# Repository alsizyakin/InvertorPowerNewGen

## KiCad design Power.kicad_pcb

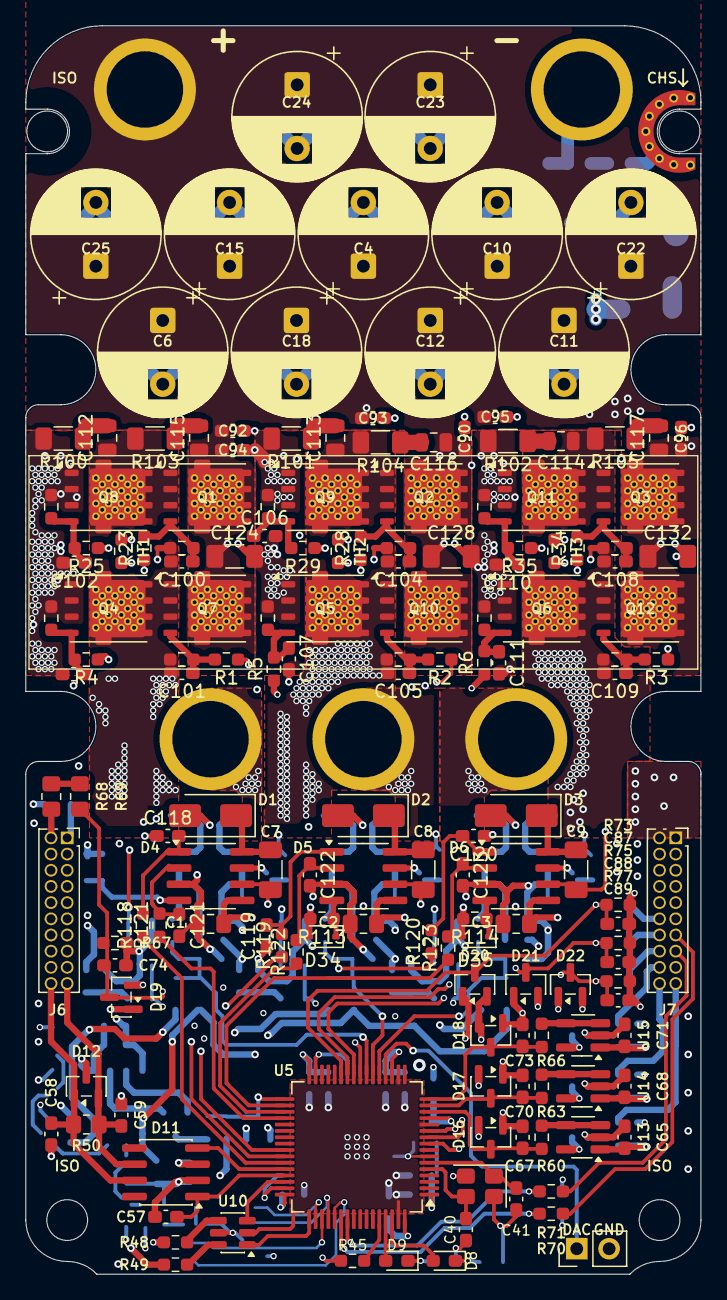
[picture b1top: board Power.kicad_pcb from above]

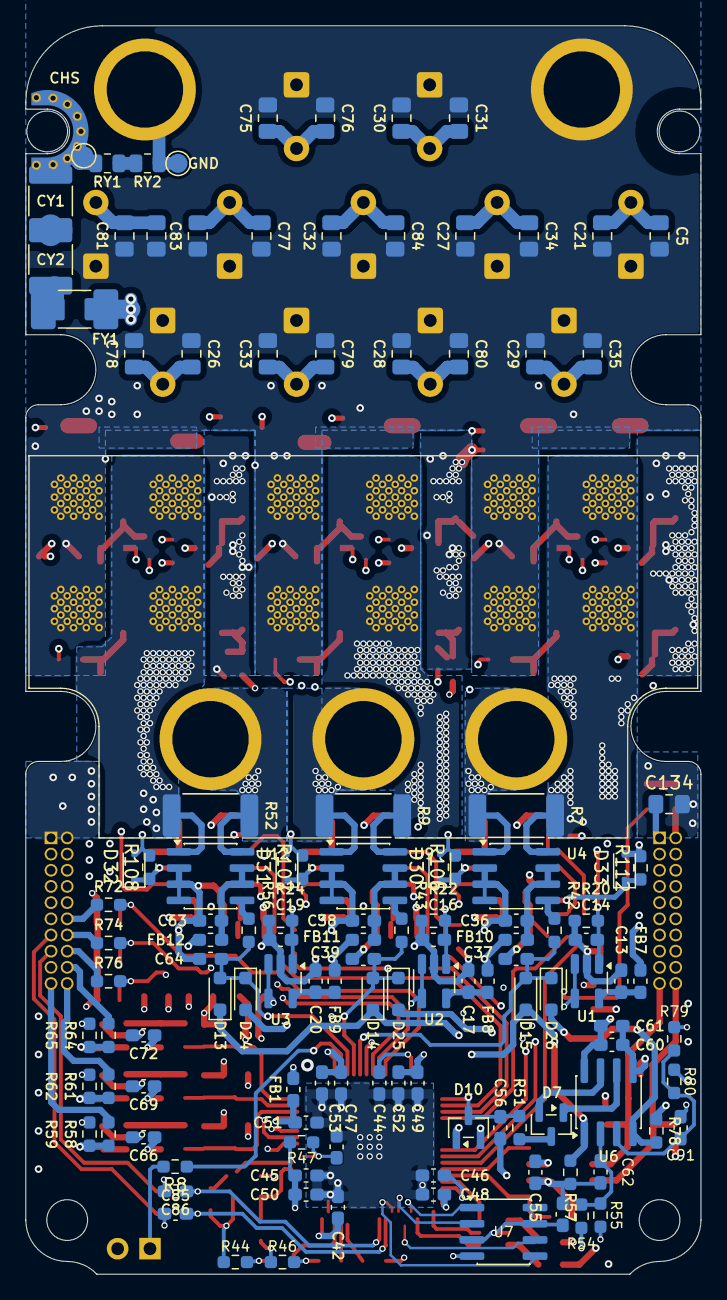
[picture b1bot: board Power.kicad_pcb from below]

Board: 6 copper layers, 53.0 x 98.0 mm, 299 parts (126 on the bottom side), 139 nets.

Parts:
C1, C2, C3: 10u; C_0805_2012Metric_Pad1.18x1.45mm_HandSolder
C4, C6, C10, C11, C12, C15, C18, C22, C23, C24, C25: 180u; CP_Radial_D10.0mm_P5.00mm
C5, C21, C26, C27, C28, C29, C30, C31, C32, C33, C34, C35, C75, C76, C77, C78, C79, C80, C81, C82, C83, C84: 2.2u; C_0805_2012Metric_Pad1.18x1.45mm_HandSolder
C7, C8, C9: 1u; C_1206_3216Metric_Pad1.33x1.80mm_HandSolder
C13, C14, C16, C17, C19, C20, C36, C38, C42, C43, C45, C47, C48, C49, C50, C61, C62, C63, C66, C69, C72, C74, C91: 100n; C_0603_1608Metric_Pad1.08x0.95mm_HandSolder
C37, C39, C64: 15n; C_0603_1608Metric_Pad1.08x0.95mm_HandSolder
C40, C41: 12p; C_0603_1608Metric_Pad1.08x0.95mm_HandSolder
C44, C46, C60, C90, C92, C93, C94, C95, C96: 2.2u; C_0603_1608Metric_Pad1.08x0.95mm_HandSolder
C51: 10u; C_0603_1608Metric_Pad1.08x0.95mm_HandSolder
C52: 4.7u; C_0603_1608Metric_Pad1.08x0.95mm_HandSolder
C53, C54, C55: 1u; C_0603_1608Metric_Pad1.08x0.95mm_HandSolder
C56: 10p; C_0603_1608Metric_Pad1.08x0.95mm_HandSolder
C57, C58, C59, C67, C70, C73: 56p; C_0603_1608Metric_Pad1.08x0.95mm_HandSolder
C65, C68, C71, C87, C88, C89: 1n; C_0603_1608Metric_Pad1.08x0.95mm_HandSolder
C85, C86: 10n; C_0603_1608Metric_Pad1.08x0.95mm_HandSolder
C100, C101, C102, C103, C104, C105, C106, C107, C108, C109, C110, C111: 10n 50V C0G; C_0603_1608Metric_Pad1.08x0.95mm_HandSolder
C112, C113, C114, C115, C116, C117: 4.7n 100V C0G; C_0805_2012Metric
C118, C119, C120, C121, C122, C123: 100p; C_0603_1608Metric_Pad1.08x0.95mm_HandSolder
C124, C128, C132: 1u 100V X7R; C_1206_3216Metric_Pad1.33x1.80mm_HandSolder
C134: 100n 100V X7R; C_0805_2012Metric_Pad1.18x1.45mm_HandSolder
CY1, CY2: 470n 250V X7R; C_1812_4532Metric
D1, D2, D3: D_SMA
D4, D5, D6, D11: SOIC-8_3.9x4.9mm_P1.27mm
D7, D10, D12, D16, D17, D18, D19, D20, D21, D22: SOT-23
D8, D9: LED_0603_1608Metric_Pad1.05x0.95mm_HandSolder
D13, D14, D15, D24, D25, D26: D_SOD-323_HandSoldering
D30, D31, D32, D33, D34, D35: PMEG4010BEA; D_SOD-323
FB1, FB7, FB8, FB9, FB10, FB11, FB12: L_0603_1608Metric_Pad1.05x0.95mm_HandSolder
FY1: 2A 125VDC; Fuse_2410_1206
H1, H3, H4: MountingHole; MountingHole_3.2mm_M3
H2: H_CHS; MountingHole_3.2mm_M3_Slot_CHS
J1, J2, J3, J4, J5: Bush_M4
J6, J7: PinSocket_2x10_P1.27mm_Vertical
NT1, NT2, NT3: NetTie_2; NetTie-2_SMD_Pad0.5mm
Q1, Q2, Q3, Q4, Q5, Q6, Q7, Q8, Q9, Q10, Q11, Q12: PDFN-8L
R1, R2, R3, R4, R5, R6, R23, R25, R28, R29, R34, R35: 1; R_0603_1608Metric_Pad0.98x0.95mm_HandSolder
R7, R9, R52: 300u; R_2512_6332Metric_Pad1.40x3.35mm_HandSolder
R8: R; R_0603_1608Metric_Pad0.98x0.95mm_HandSolder
R19, R20, R21, R22, R24, R26, R27, R30, R31, R32, R33, R36, R37, R38, R39, R45, R47, R57, R78: 10k; R_0603_1608Metric_Pad0.98x0.95mm_HandSolder
R42, R43, R56, R60, R63, R66, R70, R71: 120; R_0603_1608Metric_Pad0.98x0.95mm_HandSolder
R44, R46, R67: 1k; R_0603_1608Metric_Pad0.98x0.95mm_HandSolder
R48, R49: 20; R_0603_1608Metric_Pad0.98x0.95mm_HandSolder
R50: 120; R_0805_2012Metric_Pad1.20x1.40mm_HandSolder
R51: 100; R_0603_1608Metric_Pad0.98x0.95mm_HandSolder
R54: 5.6k; R_0603_1608Metric_Pad0.98x0.95mm_HandSolder
R55, R58, R61, R64, R72, R74, R76: 18k; R_0603_1608Metric_Pad0.98x0.95mm_HandSolder
R59, R62, R65, R73, R75, R77: 36k; R_0603_1608Metric_Pad0.98x0.95mm_HandSolder
R68, R69: 16.2k; R_0805_2012Metric_Pad1.20x1.40mm_HandSolder
R79: 2.4k; R_0603_1608Metric_Pad0.98x0.95mm_HandSolder
R80: 750; R_0603_1608Metric_Pad0.98x0.95mm_HandSolder
R100, R101, R102, R103, R104, R105: 0.47; R_1206_3216Metric_Pad1.30x1.75mm_HandSolder
R106, R107, R108, R112, R113, R114: 0.82; R_0603_1608Metric_Pad0.98x0.95mm_HandSolder
R118, R119, R120, R121, R122, R123: 0; R_0603_1608Metric_Pad0.98x0.95mm_HandSolder
RY1, RY2: 100k; R_0805_2012Metric
TH1, TH2, TH3: R_0603_1608Metric_Pad0.98x0.95mm_HandSolder
TP1: DAC1; PinHeader_1x02_P2.54mm_Vertical
TP2: TP_CHS; TestPoint_Pad_D1.5mm
TP3: TP_GND; TestPoint_Pad_D1.5mm
U1, U2, U3, U13, U14, U15: SOT-23-5_HandSoldering
U4, U6, U7, U9, U12: SOIC-8_3.9x4.9mm_P1.27mm
U5: LQFP-64_10x10mm_P0.5mm
U10: SOT-23-6
Y1: 16M; Crystal_SMD_SeikoEpson_FA238-4Pin_3.2x2.5mm

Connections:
+3.3V: C42.1, C45.1, C47.1, C48.1, C49.1, C50.1, C52.1, C53.1, C54.1, C55.2, C60.1, C61.1, C66.1, C69.1, C72.1, D10.2 (K), D11.3 (Vcc), D16.2 (K), D17.2 (K), D18.2 (K), D19.2 (K), D20.2 (K), D21.2 (K), D22.2 (K), FB1.2, FB7.1, FB8.1, FB9.1, FB10.1, FB11.1, FB12.1, J7.7, J7.8, J7.9, J7.10, R47.1, R54.1, R78.1, R79.1, TH1.1, TH2.1, TH3.1, U5.1 (VBAT), U5.19 (VDD), U5.32 (VDD), U5.48 (VDD), U5.64 (VDD), U6.8 (V+), U7.3 (~WP), U7.7 (~HOLD), U7.8 (VCC), U10.5 (VBUS), U13.5 (V+), U14.5 (V+), U15.5 (V+)
+3.3VA: C51.1, FB1.1, U5.13 (VDDA)
+12V: C1.2, C2.2, C3.2, D1.2 (A), D2.2 (A), D3.2 (A), D4.5 (VDD), D5.5 (VDD), D6.5 (VDD), J6.7, J6.8, J6.9, J6.10
/ADC_IN_1: C89.1, D22.3 (A), R76.2, R77.1, U5.25 (PC5)
/ADC_IN_2: C88.1, D21.3 (A), R74.2, R75.1, U5.26 (PB0)
/ADC_IN_3: C87.1, D20.3 (A), R72.2, R73.1, U5.27 (PB1)
/BkIN_1: C56.1, D10.3 (common), R51.1, U5.33 (PB12)
/CAN1_RXD_MCU: D11.4 (R), U5.44 (PA11)
/CAN1_TXD_MCU: C57.2, D11.1 (D), U5.45 (PA12)
/CANH: C58.2, D11.7 (CANH), D12.1 (K), J6.20, R50.2
/CANL: C59.1, D11.6 (CANL), D12.2 (K), J6.19, R50.1
/CHASSIS: CY1.1, H2.1, RY1.1, TP2.1
/CY_MID: CY1.2, CY2.1
/Current_Sensor_1/Phase_IN: C108.2, C109.2, C114.1, NT3.2, Q3.S, Q6.D, Q11.D, Q12.S, R36.1, R38.1, R52.2, R105.2, U12.1 (IN-)
/Current_Sensor_1/Phase_OUT: J3.1 (Pin_1_1), R52.1, U12.8 (IN+)
/Current_Sensor_2/Phase_IN: C104.2, C105.2, C113.1, NT2.2, Q2.S, Q5.D, Q9.D, Q10.S, R9.2, R30.1, R32.1, R104.2, U9.8 (IN+)
/Current_Sensor_2/Phase_OUT: J2.1 (Pin_1_1), R9.1, U9.1 (IN-)
/Current_Sensor_3/Phase_IN: C100.2, C101.2, C112.1, NT1.2, Q1.S, Q4.D, Q7.S, Q8.D, R7.1, R19.1, R26.1, R103.2, U4.8 (IN+)
/Current_Sensor_3/Phase_OUT: J1.1 (Pin_1_1), R7.2, U4.1 (IN-)
/Current_measure_1: C64.2, D13.2 (A), D24.1 (K), R56.1, U5.21 (PA5)
/Current_measure_2: C39.2, D14.2 (A), D25.1 (K), R43.1, U5.22 (PA6)
/Current_measure_3: C37.2, D15.2 (A), D26.1 (K), R42.1, U5.23 (PA7)
/DAC_1_MCU: R8.1, U5.20 (PA4)
/Digital_IN/OUT_1: C85.2, R70.1, U5.54 (PD2)
/Digital_IN/OUT_2: C86.1, R71.2, U5.55 (PB3)
/Driver_1/HO: D32.2 (A), R3.1, R34.1, R108.2
/Driver_1/HO_DRV: D6.7 (HO), D32.1 (K), R108.1
/Driver_1/LO: D35.2 (A), R6.1, R35.1, R114.2
/Driver_1/LO_DRV: D6.4 (LO), D35.1 (K), R114.1
/Driver_1/SW: C9.2, D6.6 (SW), NT3.1
/Driver_2/HO: D31.2 (A), R2.1, R28.1, R107.2
/Driver_2/HO_DRV: D5.7 (HO), D31.1 (K), R107.1
/Driver_2/LO: D34.2 (A), R5.1, R29.1, R113.2
/Driver_2/LO_DRV: D5.4 (LO), D34.1 (K), R113.1
/Driver_2/SW: C8.2, D5.6 (SW), NT2.1
/Driver_3/HO: D30.2 (A), R1.1, R23.1, R106.2
/Driver_3/HO_DRV: D4.7 (HO), D30.1 (K), R106.1
/Driver_3/LO: D33.2 (A), R4.1, R25.1, R112.2
/Driver_3/LO_DRV: D4.4 (LO), D33.1 (K), R112.1
/Driver_3/SW: C7.2, D4.6 (SW), NT1.1
/EEPROM_MISO_MCU: U5.52 (PC11), U7.2 (MISO)
/EEPROM_MOSI_MCU: U5.53 (PC12), U7.5 (MOSI)
/EEPROM_SCK_MCU: U5.51 (PC10), U7.6 (SCK)
/EEPROM_~CS_MCU: U5.50 (PA15), U7.1 (~CS)
/HALL_1: J7.19, R58.1
/HALL_2: J7.20, R61.1
/HALL_3: J7.18, R64.1
/Hall_1_MCU: C67.1, D16.3 (A), R60.2, U5.14 (PA0)
/Hall_2_MCU: C70.1, D17.3 (A), R63.2, U5.15 (PA1)
/Hall_3_MCU: C73.1, D18.3 (A), R66.2, U5.16 (PA2)
/RY_MID: RY1.2, RY2.1
/SWCLK: U5.49 (PA14), U10.1 (I/O1)
/SWCLK_IN: J6.15, R49.2
/SWDIO: U5.46 (PA13), U10.3 (I/O2)
/SWDIO_IN: J6.13, R48.2
/TMR1_CH1: R120.1, U5.41 (PA8)
/TMR1_CH1N: R123.1, U5.34 (PB13)
/TMR1_CH2: R119.1, U5.42 (PA9)
/TMR1_CH2N: R122.1, U5.35 (PB14)
/TMR1_CH3: R118.1, U5.43 (PA10)
/TMR1_CH3N: R121.1, U5.36 (PB15)
/Temp_PCB_1_MCU: U3.3 (-), U3.4, U5.9 (PC1)
/Temp_PCB_2_MCU: U2.3 (-), U2.4, U5.10 (PC2)
/Temp_PCB_3_MCU: U1.3 (-), U1.4, U5.11 (PC3)
/VDC_MCU: C74.1, D19.3 (A), R67.1, R69.2, U5.24 (PC4)
/Y_F: CY2.2, FY1.2
BOOT0: R45.2, U5.60 (BOOT0)
GND: C1.1, C2.1, C3.1, C4.2, C5.2, C6.2, C10.2, C11.2, C12.2, C13.2, C14.1, C15.2, C16.1, C17.2, C18.2, C19.1, C20.2, C21.2, C22.2, C23.2, C24.2, C25.2, C26.2, C27.2, C28.2, C29.2, C30.2, C31.2, C32.2, C33.2, C34.2, C35.2, C36.1, C37.1, C38.1, C39.1, C40.1, C41.2, C42.2, C43.1, C44.2, C45.2, C46.2, C47.2, C48.2, C49.2, C50.2, C51.2, C52.2, C53.2, C54.2, C55.1, C56.2, C57.1, C58.1, C59.2, C60.2, C61.2, C62.2, C63.1, C64.1, C65.2, C66.2, C67.2, C68.2, C69.2, C70.2, C71.2, C72.2, C73.2, C74.2, C75.2, C76.2, C77.2, C78.2, C79.2, C80.2, C81.2, C82.2, C83.2, C84.2, C85.1, C86.2, C87.2, C88.2, C89.2, C90.2, C91.2, C92.2, C93.2, C94.2, C95.2, C96.2, C102.2, C103.2, C106.2, C107.2, C110.2, C111.2, C118.1, C119.1, C120.1, C121.2, C122.2, C123.2, C124.2, C128.2, C132.2, C134.2, D4.3 (GND), D5.3 (GND), D6.3 (GND), D10.1 (A), D11.2 (GND), D12.3 (A), D16.1 (K), D17.1 (K), D18.1 (K), D19.1 (K), D20.1 (K), D21.1 (K), D22.1 (K), FY1.1, J5.1 (Pin_1_1), J6.11, J6.12, J6.17, J6.18, J7.1, J7.2, J7.3, J7.4, J7.5, J7.6, J7.11, J7.17, Q4.S, Q5.S, Q6.S, Q8.S, Q9.S, Q11.S, R20.1, R21.1, R22.1, R24.1, R27.1, R31.1, R33.1, R37.1, R39.1, R44.2, R45.1, R46.2, R55.2, R57.1, R59.2, R62.2, R65.2, R67.2, R73.2, R75.2, R77.2, R80.2, R100.2, R101.2, R102.2, RY2.2, TP1.2, TP3.1, U1.2 (V-), U2.2 (V-), U3.2 (V-), U4.2 (GND), U4.3 (REF2), U4.4 (NC), U5.12 (VSSA), U5.18 (VSS), U5.63 (VSS), U6.5 (V-), U7.4 (GND), U9.2 (GND), U9.3 (REF2), U9.4 (NC), U10.2 (GND), U12.2 (GND), U12.3 (REF2), U12.4 (NC), U13.2 (V-), U14.2 (V-), U15.2 (V-), Y1.2, Y1.4
NRST: C43.2, R47.2, U5.7 (NRST)
unnamed: C100.1, Q1.G, R19.2, R23.2
unnamed: C101.1, Q7.G, R1.2, R26.2
unnamed: C102.1, Q8.G, R21.2, R25.2
unnamed: C103.1, Q4.G, R4.2, R27.2
unnamed: C104.1, Q2.G, R28.2, R30.2
unnamed: C105.1, Q10.G, R2.2, R32.2
unnamed: C106.1, Q9.G, R29.2, R31.2
unnamed: C107.1, Q5.G, R5.2, R33.2
unnamed: C108.1, Q3.G, R34.2, R36.2
unnamed: C109.1, Q12.G, R3.2, R38.2
unnamed: C110.1, Q11.G, R35.2, R37.2
unnamed: C111.1, Q6.G, R6.2, R39.2
unnamed: C112.2, R100.1
unnamed: C113.2, R101.1
unnamed: C114.2, R102.1
unnamed: C115.2, R103.1
unnamed: C116.2, R104.1
unnamed: C117.2, R105.1
unnamed: C7.1, D1.1 (K), D4.8 (BST)
unnamed: C8.1, D2.1 (K), D5.8 (BST)
unnamed: C9.1, D3.1 (K), D6.8 (BST)
unnamed: C118.2, D4.1 (HI), R118.2
unnamed: C121.1, D4.2 (LI), R121.2
unnamed: C119.2, D5.1 (HI), R119.2
unnamed: C122.1, D5.2 (LI), R122.2
unnamed: C120.2, D6.1 (HI), R120.2
unnamed: C123.1, D6.2 (LI), R123.2
unnamed: D7.1, U6.6
unnamed: D7.2, U6.7
unnamed: D7.3, R51.2
unnamed: D8.2 (A), U5.62 (PB9)
unnamed: D8.1 (K), R44.1
unnamed: D9.2 (A), U5.61 (PB8)
unnamed: D9.1 (K), R46.1
unnamed: D13.1 (K), D14.1 (K), D15.1 (K), R57.2, U6.1 (+)
unnamed: D24.2 (A), D25.2 (A), D26.2 (A), R78.2, U6.4 (-)
unnamed: J7.12, R72.1
unnamed: J7.13, R70.2
unnamed: J7.14, R74.1
unnamed: J7.15, R71.1
unnamed: J7.16, R76.1
unnamed: R8.2, TP1.1
unnamed: R48.1, U10.4 (I/O2)
unnamed: R49.1, U10.6 (I/O1)
unnamed: R68.2, R69.1
unnamed: C14.2, R20.2, TH1.2, U1.1 (+)
unnamed: C13.1, FB7.2, U1.5 (V+)
unnamed: C16.2, R22.2, TH2.2, U2.1 (+)
unnamed: C17.1, FB8.2, U2.5 (V+)
unnamed: C19.2, R24.2, TH3.2, U3.1 (+)
unnamed: C20.1, FB9.2, U3.5 (V+)
unnamed: R42.2, U4.5 (OUT)
unnamed: C36.2, FB10.2, U4.6 (VS), U4.7 (REF1)
unnamed: C40.2, U5.5 (PH0), Y1.3
unnamed: C41.1, U5.6 (PH1), Y1.1
unnamed: C44.1, U5.31 (VCAP_1)
unnamed: C46.1, U5.47 (VCAP_2)
unnamed: C62.1, R54.2, R55.1, U6.2 (-)
unnamed: C91.1, R79.2, R80.1, U6.3 (+)
unnamed: R43.2, U9.5 (OUT)
unnamed: C38.2, FB11.2, U9.6 (VS), U9.7 (REF1)
unnamed: R56.2, U12.5 (OUT)
unnamed: C63.2, FB12.2, U12.6 (VS), U12.7 (REF1)
unnamed: C65.1, R58.2, R59.1, U13.1 (+)
unnamed: R60.1, U13.3 (-), U13.4
unnamed: C68.1, R61.2, R62.1, U14.1 (+)
unnamed: R63.1, U14.3 (-), U14.4
unnamed: C71.1, R64.2, R65.1, U15.1 (+)
unnamed: R66.1, U15.3 (-), U15.4
VDC: C4.1, C5.1, C6.1, C10.1, C11.1, C12.1, C15.1, C18.1, C21.1, C22.1, C23.1, C24.1, C25.1, C26.1, C27.1, C28.1, C29.1, C30.1, C31.1, C32.1, C33.1, C34.1, C35.1, C75.1, C76.1, C77.1, C78.1, C79.1, C80.1, C81.1, C82.1, C83.1, C84.1, C90.1, C92.1, C93.1, C94.1, C95.1, C96.1, C115.1, C116.1, C117.1, C124.1, C128.1, C132.1, C134.1, J4.1 (Pin_1_1), J6.1, J6.2, J6.3, J6.4, Q1.D, Q2.D, Q3.D, Q7.D, Q10.D, Q12.D, R68.1

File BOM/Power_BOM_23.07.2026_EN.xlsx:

Reference | Value | Product Name | Replacement | Package | Description | Quantity | DNP
C13, C14, C16, C17, C19, C20, C36, C37, C38, C39, C42, C43, C45, C47, C48, C49,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 | 100n |  |  | SMD 0603 | Capacitor SMD 50V | 26
C85, C86 | 10n |  |  | SMD 0603 | Capacitor SMD 50V | 2
C56 | 10p |  |  | SMD 0603 | Capacitor SMD 50V | 1
C51 | 10u |  |  | SMD 0603 | Capacitor SMD 50V | 1
C1, C2, C3 | 10u |  |  | SMD 0805 | Capacitor SMD 50V | 3
C40, C41 | 12p |  |  | SMD 0603 | Capacitor SMD 50V | 2
C4, C6, C10, C11, C12, C15, C18, C22, C23, C24, C25 | 180u | EEUFS1K181 |  | CP Radial D10.0mm P5.00mm | Capacitort electrolytic 80V | 11
C65, C68, C71, C87, C88, C89 | 1n |  |  | SMD 0603 | Capacitor SMD 50V | 6
C53, C54, C55 | 1u |  |  | SMD 0603 | Capacitor SMD 50V | 3
C7, C8, C9 | 1u |  |  | SMD 1206 | Capacitor SMD 50V | 3
C44, C46, C60 | 2.2u |  |  | SMD 0603 | Capacitor SMD 50V | 3
C5, C21, C26, C27, C28, C29, C30, C31, C32, C33, C34, C35, C75, C76, C77, C78, 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 | 2.2u |  |  | SMD 0805 | Capacitor SMD 100V | 22
C52 | 4.7u |  |  | SMD 0603 | Capacitor SMD 50V | 1
C57, C58, C59, C67, C70, C73 | 56p |  |  | SMD 0603 | Capacitor SMD 50V | 6
D1, D2, D3 | ~ | MURA110T3G |  | SMA | Ultra Fast diode | 3
D8, D9 | ~ | FYLS-0603UBC |  | SMD 0603 | Blue LED | 2
D13, D14, D15, D24, D25, D26 | ~ | BAT54WS-E3-08 |  | SOD-323 | Schottky Diode | 6
D11 | ~ | SIT65HVD232DR |  | SOIC-8 3.9x4.9mm P1.27mm | CAN interface | 1
D4, D5, D6 | ~ | NSD1624 |  | SOIC-8 3.9x4.9mm P1.27mm | Gate driver | 3
D7 | ~ | BAT54C |  | SOT-23 |  | 1
D12 | ~ | PESD2CAN |  | SOT-23 | Dual Line CAN Bus Protector, 24Vrwm | 1
D10, D16, D17, D18, D19, D20, D21, D22 | ~ | BAT54S |  | SOT-23 | TVS | 8
FB1, FB7, FB8, FB9, FB10, FB11, FB12 | ~ | MMZ2012R301AT000 |  | SMD 0603 | Ferrite bead | 7
J1, J2, J3, J4, J5 | ~ |  |  | Bush M4 |  | 5
J6, J7 | ~ | DS1065-03-2x10S8BV |  | PinSocket 2x10 P1.27mm | Connector | 2
Q1, Q2, Q3, Q4, Q5, Q6, Q7, Q8, Q9, Q10, Q11, Q12 | ~ | WMB043N10HGS |  | PDFN-8L | N MOSFET | 12
R51 | 100 |  |  | SMD 0603 | Resistor SMD 1% | 1
R19, R20, R21, R22, R24, R26, R27, R30, R31, R32, R33, R36, R37, R38, R39, R45,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 | 10k |  |  | SMD 0603 | Resistor SMD 1% | 19
R42, R43, R56, R60, R63, R66, R70, R71 | 120 |  |  | SMD 0603 | Resistor SMD 1% | 8
R50 | 120 |  |  | SMD 0805 | Resistor SMD 1% | 1
R68, R69 | 16.2k |  |  | SMD 0805 | Resistor SMD 1% | 2
R55, R58, R61, R64, R72, R74, R76 | 18k |  |  | SMD 0603 | Resistor SMD 1% | 7
R44, R46, R67 | 1k |  |  | SMD 0603 | Resistor SMD 1% | 3
R79 | 2.4k |  |  | SMD 0603 | Resistor SMD 1% | 1
R1, R2, R3, R4, R5, R6, R23, R25, R28, R29, R34, R35 | 2.7 |  |  | SMD 0805 | Resistor SMD 1% | 12
R48, R49 | 20 |  |  | SMD 0603 | Resistor SMD 1% | 2
R7, R9, R52 | 300u | WSLF2512L3000FEA |  | SMD 2512 | Resistor SMD 1% | 3
R59, R62, R65, R73, R75, R77 | 36k |  |  | SMD 0603 | Resistor SMD 1% | 6
R54 | 5.6k |  |  | SMD 0603 | Resistor SMD 1% | 1
R80 | 750 |  |  | SMD 0603 | Resistor SMD 1% | 1
TH1, TH2, TH3 | ~ | NCP18XH103F03RB |  | SMD 0603 | NTC | 3
U5 | ~ | APM32F405RGT6 |  | LQFP-64 10x10mm P0.5mm | MCU | 1
U6 | ~ | TLV3502AIDR |  | SOIC-8 3.9x4.9mm P1.27mm | Comparator | 1
U7 | ~ | FM25W256 |  | SOIC-8 3.9x4.9mm P1.27mm | FRAM | 1
U4, U9, U12 | ~ | AD8418 |  | SOIC-8 3.9x4.9mm P1.27mm | Shunt monitor | 3
U1, U2, U3, U13, U14, U15 | ~ | LMV321 |  | SOT-23-5 | Op-Amp | 6
U10 | ~ | USBLC6-2SC6 |  | SOT-23-6 | ESD protection | 1
Y1 | 16M | X322516MOB4SI |  | Crystal SMD SeikoEpson FA238-4Pin 3.2x2.5mm | Crystal | 1
